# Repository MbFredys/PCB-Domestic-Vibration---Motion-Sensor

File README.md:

# Motion and Vibration Sensor — Hardware Design

Compact motion-sensing PCB concept combining an Arduino Nano ESP32 and an MPU-6050 six-axis IMU.

> **Status: design under review.** Source schematics, PCB files, renders and manufacturing exports are available. Firmware is not published in this repository, and no measurement results are supplied. The current design has unresolved electrical issues and must not be treated as ready for fabrication.

## Objective and intended architecture

The intended application is acquiring motion data from an object and exploring wireless monitoring. The design includes:

- Arduino Nano ESP32 module for processing and intended Wi-Fi/Bluetooth connectivity.
- MPU-6050 accelerometer and gyroscope connected over I²C, with an interrupt signal.
- A battery input labelled `+7.4_BATT` connected to the Nano VIN input.
- A 3.3 V rail supplied by the Nano module to the IMU.
- External reset circuitry.

The carrier does not contain a separately populated 3.3 V regulator in the published netlist. The battery range, module input limits and power budget require verification.

## Important design-review findings

- C1 and C2 are assigned **2.2 µF** and connected between 3.3 V and SCL/SDA in the published netlist. This is not a substitute for I²C pull-up resistors and requires correction before fabrication.
- The reset resistor R1 has an unspecified value (`R`).
- The legacy source filenames say “Wearable Básico”; these are retained so existing links remain valid.

See [DESIGN_REVIEW.md](DESIGN_REVIEW.md) for evidence, proposed remediation and verification criteria. These findings are not marked as resolved.

## What is not demonstrated

No firmware, alerting service, wireless dashboard, logging implementation, calibrated vibration measurements, predictive-maintenance performance or measured battery life is provided. Those are possible future developments, not current capabilities.

## Repository contents

| Directory | Contents |
|---|---|
| [Kicad Files](Kicad%20Files/) | Editable schematics, PCB, project and exported netlist |
| [Schematic](Schematic/) | PDF schematic |
| [Manufacturing](Manufacturing/) | Historical BOM, placement and fabrication exports; review before reuse |
| [Release](Release/) | PCB renders and enclosure illustration |
| [Firmware](Firmware/) | Availability note; no implementation |

## Next development steps

Resolve the documented electrical findings, synchronize schematic and PCB, run ERC/DRC, regenerate outputs, then build and test a prototype. Define the measurement bandwidth, sampling rate, mechanical mounting and acceptance criteria before claiming vibration-monitoring performance.

## License

MIT. See [LICENSE](LICENSE).

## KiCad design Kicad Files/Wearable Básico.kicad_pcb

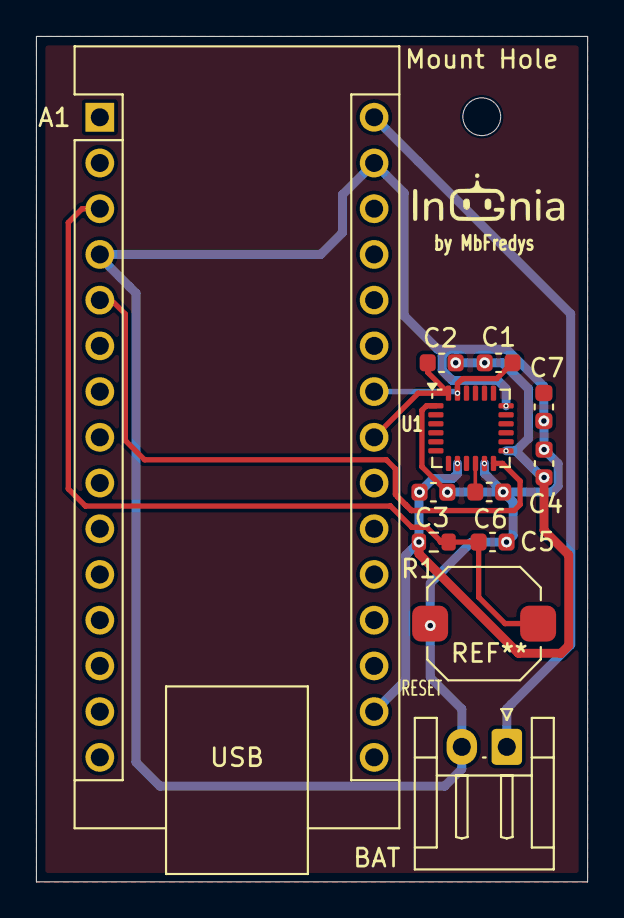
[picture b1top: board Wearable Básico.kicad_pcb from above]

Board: 2 copper layers, 30.6 x 47.0 mm, 13 parts (0 on the bottom side), 9 nets.

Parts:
A1: Arduino_Nano_ESP32; Arduino_Nano
BAT: BATTERY; JST_EH_S2B-EH_1x02_P2.50mm_Horizontal
C1, C2, C5: 2.2uF; C_0603_1608Metric
C3: 10nF; C_0603_1608Metric
C4, C6: 0.1uF; C_0603_1608Metric
C7: 2.2nF; C_0603_1608Metric
Mount Hole: MountingHole_2.1mm
R1: R; R_0603_1608Metric
RESET: RESET; SW_Push_1TS009xxxx-xxxx-xxxx_6x6x5mm
U1: MPU-6050; InvenSense_QFN-24_4x4mm_P0.5mm

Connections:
+3V3: A1.17 (3V3), C1.1, C2.1, C3.1, C4.1, R1.1, U1.8 (VLOGIC), U1.13 (VDD)
+7.4_BATT: A1.30 (VIN), BAT.1
GND: A1.4 (GND), A1.29 (GND), BAT.2, C3.2, C4.2, C5.2, C6.2, C7.2, RESET.2, U1.1 (CLKIN), U1.11 (FSYNC), U1.18 (GND)
I2C_SCL_IMU: A1.24 (SCL/A5), C1.2, U1.23 (SCL)
I2C_SDA_IMU: A1.23 (SDA/A4), C2.2, U1.24 (SDA)
INTERRUPTION_IMU: A1.5 (D2), U1.12 (INT)
unnamed: A1.3 (~RESET), C5.1, R1.2, RESET.1
unnamed: C7.1, U1.20 (CPOUT)
unnamed: C6.1, U1.10 (REGOUT)

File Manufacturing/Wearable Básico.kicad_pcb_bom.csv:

Designator,Quantity,Value,Footprint,Package,MPN,DNP,Mount_Type,Description
A1,1,Arduino_Nano_ESP32,Arduino_Nano,,,,tht,"Arduino Nano board based on the ESP32-S3 with a dual-core 240 MHz processor, 384 kB ROM, 512 kB SRAM. Operates at 3.3V, with 5V USB-C® input and 6-21V VIN. Features Wi-Fi®, Bluetooth® LE, digital and analog pins, and supports SPI, I2C, UART, I2S, and CAN."
BAT,1,BATTERY,JST_EH_S2B-EH_1x02_P2.50mm_Horizontal,,,,tht,"Generic screw terminal, single row, 01x02, script generated (kicad-library-utils/schlib/autogen/connector/)"
"C1, C2, C5",3,2.2uF,C_0603_1608Metric,,,,smt,Unpolarized capacitor
C3,1,10nF,C_0603_1608Metric,,,,smt,Unpolarized capacitor
"C4, C6",2,0.1uF,C_0603_1608Metric,,,,smt,Unpolarized capacitor
C7,1,2.2nF,C_0603_1608Metric,,,,smt,Unpolarized capacitor
R1,1,R,R_0603_1608Metric,,,,smt,Resistor
RESET,1,RESET,SW_Push_1TS009xxxx-xxxx-xxxx_6x6x5mm,,,,smt,"Push button switch, generic, two pins"
U1,1,MPU-6050,InvenSense_QFN-24_4x4mm_P0.5mm,,,,smt,"InvenSense 6-Axis Motion Sensor, Gyroscope, Accelerometer, I2C"

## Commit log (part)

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2025-10-18 Revise README for Domestic Vibration Sensor project
    Expanded the README to include detailed features, usage instructions, getting started guide, contribution guidelines, and areas for contribution.
2025-10-18 Add initial firmware documentation
2025-10-18 Add Kicad.md file with initial content
2025-10-18 Add initial manufacturing documentation
2025-10-18 Add PDF Schematic documentation
2025-10-18 Create release.md with design variants information
    Add documentation for finalized design variants.
